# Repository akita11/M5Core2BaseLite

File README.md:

# M5CoreBaseLite

- [M5StackCore2](https://www.switch-science.com/catalog/6530/)の底板と交換し、各種UNIT等を接続するPortを増設します。
- PortはA, B, C, D, Eの5種類があり、そのうちPortAは2個（うち1個は電源電圧を3.3Vに変更できます）あります。※v1.0aから、PortAはいずれも電源電圧5Vとなりました（うち1つ(PortA')は3.3Vに変更可能：後述）
- これらのPortは、UIFlowから利用できます。また以下のGPIOの割当を使って、ArduinoIDE等からも利用できます。
- コネクタの色は、この写真ではすべて白ですが、後述のようにPortA/B/C/D/Eで色を分けることもできます。

これを使う[ハンズオン資料(GomiHgy氏作)](https://docs.google.com/presentation/d/11nBajGIhjv-naQnr_dzS9U8Bt7wMfS5UbUuWfKnAS3c/edit#slide=id.p)などで、M5StackCore2を使ったIoT演習などに活用できます。

## 組み立て方 / How to Build 

1. 以下の部品を用意します。

  - ボード

  - アクリル板（3種）※v1.0aから一部部材の形状が変更になっています

  - M3ネジ（20mm x 2本、15mm x 2本）

2. M5StackCore2の底板と、加速度センサが載っている小ボードををはずします。
またリチウムイオンバッテリを底板から外しておきます（本体コネクタからは外さない）。
なおリチウムイオンバッテリに取り付けられている両面テープが、Core2のロットによってはバッテリの逆面についているようで、あとで取り付けるアクリル板(1mm)にくっつくのが気になる場合は、適当な方法でカバーします（この例では養生テープを貼っています）。
（※2mmの六角レンチが必要です。100均やホームセンター等で購入してください）

3. リチウムイオンバッテリをボードの溝を通しつつ、本体M5StackCore2本体にボードをとりつけ、アクリル板（2種）を置きます。

4. アクリル板（1mm厚）を置き、上の図のネジがおいてある場所の近くの長さのネジで、アクリル板（すべて）、ボード、M5StackCore2を固定します。
（※とりつけるネジの長さに注意）

## サイドの8pコネクタ（オプション）

オプションで8pメスソケットを取り付け、5本のIO(G26, G32, G33, G35, G36)と5V/3.3Vの電源を横に引き出すことができます。
ジャンパワイヤ等で使用できます。
アクリル板の切り込みに沿ってカットします。（細い部分が折れやすいため、折れてしまった場合は、そのままネジで固定するか、透明ボンド等で固定してください）
なお底板ラベルの隅に、このコネクタのピン配置があるので、カットしてコネクタに貼ってください。

## 各ポートとGPIOの対応

※底板のラベルにも書いてあります
- PortA,A'(赤): G32/G33
- PortB(黒): G26/G36
- PortC(青): G14/G13
- PortD(緑／黄緑): G35/G34
- PortE(黄): G19/G27

なおPortA'（ピンク色で表示）の電源電圧は、ボード裏面のハンダジャンパの"5V"側をカットし、"3.3V"側にハンダを盛ることで、3.3Vに切り替えることができます。
※初期のv1.0では、初期設定が3.3Vになっています。"3.3V"側をカットし、"5V"側にハンダを盛ることで、5Vに切り替えることができます。

※PortDのG34は、Core2-ext（Core2に付属の、底板につけるマイクと加速度センサの載った小さなボード）のマイクに接続されていますので、Core2-extを接続時にはPortDのG34は使用できません。

# Author

Junichi Akita (@akita11, akita@ifdl.jp)

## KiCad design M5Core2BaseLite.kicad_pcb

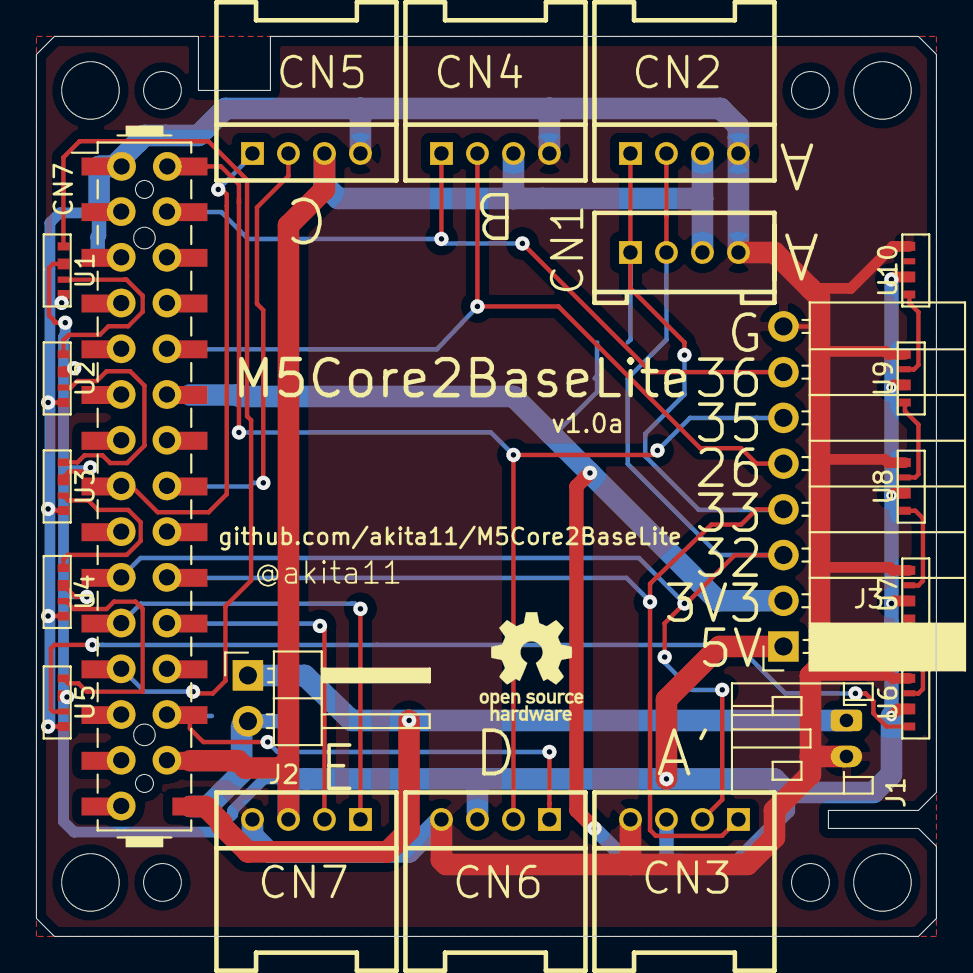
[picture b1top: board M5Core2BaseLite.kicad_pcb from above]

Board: 2 copper layers, 50.0 x 50.0 mm, 34 parts (0 on the bottom side), 28 nets.

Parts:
CN1: CON_GROVEV; CON_GROVE_V
CN2, CN3, CN4, CN5, CN6, CN7#2: CON_GROVEH; CON_GROVE_H
CN7: PinHeader_2x15_P2.54mm_Vertical_SMD
CN8: MBUS_bottom; PinSocket_2x15_P2.54mm_Vertical_SMD
J1: Conn_01x02_Female; JST_PH_S2B-PH-K_1x02_P2.00mm_Horizontal
J2: Conn_01x02_Female; PinHeader_1x02_P2.54mm_Horizontal
J3: Conn_01x08_Female; PinSocket_1x08_P2.54mm_Horizontal
JP1: SolderJumper_2_Bridged; SolderJumper-2_P1.3mm_Bridged_Pad1.0x1.5mm
JP2: SolderJumper_3_Bridged12; SolderJumper-3_P1.3mm_Bridged2Bar12_Pad1.0x1.5mm
MH1, MH1#2, MH1#3, MH2: MountingHole_3.2mm_M3
MH5, MH5#2, MH5#3, MH5#4: MountingHole_2.1mm
R1, R2: 4.7k; 0603
U1, U2, U3, U4, U5, U6, U7, U8, U9, U10: LED_SK6812side; LED_SK6812SIDE

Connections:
+3V3: CN7.12, CN8.12, J3.2, JP2.3, R1.2, R2.2
+5V: CN1.3, CN2.3, CN4.3, CN5.3, CN6.3, CN7.28, CN7#2.3, CN8.28, J3.1, JP2.1, U1.2, U2.2, U3.2, U4.2, U5.2, U6.2, U7.2, U8.2, U9.2, U10.2
/BAT: CN8.30, J2.2, JP1.2
/GPIO2: CN1.2, CN2.2, CN3.2, CN7.19, CN8.19, J3.3, R2.1
/GPIO5: CN1.1, CN2.1, CN3.1, CN7.20, CN8.20, J3.4, R1.1
/GPIO12: CN7.21, CN7#2.1, CN8.21
/GPIO13: CN7.22, CN7#2.2, CN8.22
/GPIO15: CN7.23, CN8.23, U1.1
/GPIO26: CN4.2, CN7.10, CN8.10, J3.5
/GPIO34: CN6.1, CN7.26, CN8.26
/GPIO35: CN6.2, CN7.2, CN8.2, J3.6
/GPIO36: CN4.1, CN7.4, CN8.4, J3.7
/RXD: CN5.1, CN7.15, CN8.15
/SCL: CN7.18, CN8.18
/SDA: CN7.17, CN8.17
/TXD: CN5.2, CN7.16, CN8.16
GND: CN1.4, CN2.4, CN3.4, CN4.4, CN5.4, CN6.4, CN7.1, CN7.3, CN7.5, CN7#2.4, CN8.1, CN8.3, CN8.5, J1.2, J3.8, U1.4, U2.4, U3.4, U4.4, U5.4, U6.4, U7.4, U8.4, U9.4, U10.4
unnamed: CN3.3, JP2.2
unnamed: CN7.30, J1.1, J2.1, JP1.1
unnamed: U1.3, U2.1
unnamed: U2.3, U3.1
unnamed: U3.3, U4.1
unnamed: U4.3, U5.1
unnamed: U5.3, U6.1
unnamed: U6.3, U7.1
unnamed: U7.3, U8.1
unnamed: U8.3, U9.1
unnamed: U9.3, U10.1

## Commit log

2020-10-14 add board data
2020-10-14 cover&label data
2020-10-14 add photos
2020-10-22 add silk notice for CN6/7
2020-10-24 add photo
2020-10-29 写真を整理、8pコネクタ追記
2020-10-29 ラベルを更新
2020-11-17 v1.0aの情報を追記
2020-11-17 アクリルカバーデータの更新(v1.0a)
2020-11-17 基板データをv1.0a（PortA'をデフォルト5V）に変更
2020-11-17 底板ラベルをv1.0a用に更新
2020-11-17 PortA'の電源電圧設定方法を追記
2020-11-18 底板ラベルの位置を微調整
2021-02-07 readmeにハンズオン資料へのリンクを追加
2022-01-11 add PortD's G34 notice with BOTTOM2
2022-01-12 Core2-extについての名称の変更
